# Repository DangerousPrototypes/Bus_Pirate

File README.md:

# Bus Pirate
The Bus Pirate is an open source hacker multi-tool that talks to electronic stuff. It's got a bunch of features an intrepid hacker might need to prototype their next project.

## Protocols
    
* 1-Wire
* I2C*
* SPI
* JTAG
* Asynchronous serial
* MIDI
* PC keyboard
* HD44780 LCD
* 2- and 3-wire libraries with bitwise pin control
* Scriptable binary bitbang, 1-Wire, I2C, SPI, and UART modes 

## Features

* 0-5.5volt tolerant pins
* 0-6volt measurement probe
* 1Hz-40MHz frequency measurement
* 1kHz - 4MHz pulse-width modulator, frequency generator
* On-board multi-voltage pull-up resistors
* On-board 3.3volt and 5volt power supplies with software reset
* Macros for common operations
* Bus traffic sniffers (SPI, I2C)
* A bootloader for easy firmware updates
* Transparent USB->serial mode
* 10Hz-1MHz low-speed logic analyzer
* Servo driver
* Can program many AVR microcontrollers
  * Supported by AVRdude
  * Can emulate the AVR STK500 v2 with alternate ST500 Clone firmware 
  * Programs FPGAs and CPLDs with alternate XSVF firmware
* Scriptable from Perl, Python, etc.
* Translations (currently Spanish and Italian)
* Public domain (Creative Commons Zero) source. Prototype with the Bus Pirate, then use the code in your project however you want. 

## Application Support
The Bus Pirate is used through a simple terminal interface, but these applications also support the Bus Pirate as a programming device, etc.

* [AVRDude] AVR programmer (AVRDude v5.8+, firmware v4 (any) or v5.9+)
* [OpenOCD] JTAG debugger
* [flashrom] bios/flash programmer 

# Purchasing

* Bus Pirate v4.0 - *Newer, more space for bigger firmwares*
  * Worldwide: <http://www.seeedstudio.com/depot/bus-pirate-v4-for-developers-p-740.html>
* Bus Pirate v3.6 - *Proven, more well tested*
  * Worldwide: <http://www.seeedstudio.com/depot/bus-pirate-v3-assembled-p-609.html?cPath=61_68>
  * USA: <https://www.adafruit.com/products/237?&main_page=product_info&cPath=8&products_id=237>
  * USA: <http://www.epictinker.com/Bus-Pirate-v3-assembled-p/thm180c4m.htm>
  * Germany: <http://www.watterott.com/en/Bus-Pirate>
  * Europe: <http://evola.fr/en/dangerous-prototypes/164-bus-pirate-v3-6.html>
  * USA: <https://anibit.com/product/ptt07001>
  * USA: <http://store.hackaday.com/products/buspirate-v3-6-thm180c4m>

[OpenOCD]: http://openocd.org
[AVRDude]: http://www.nongnu.org/avrdude
[flashrom]: https://www.flashrom.org/Flashrom

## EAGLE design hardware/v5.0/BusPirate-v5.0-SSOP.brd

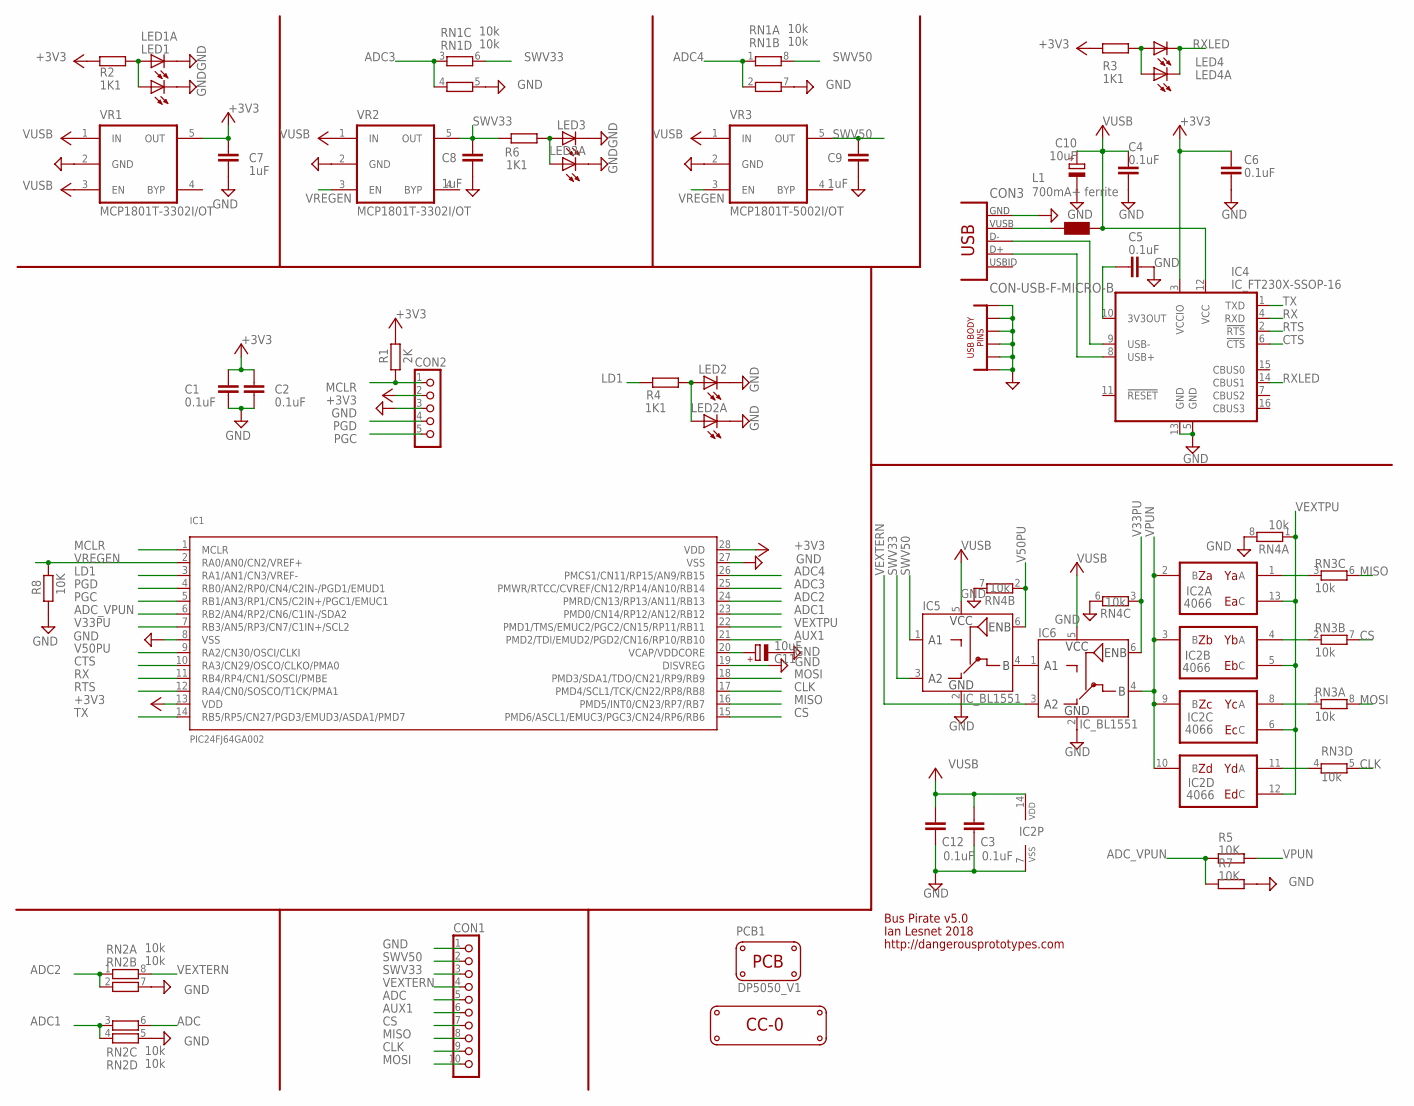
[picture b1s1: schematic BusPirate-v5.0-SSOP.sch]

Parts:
C1, C2, C3, C4, C5, C6, C12: 0.1uF; C603
C7, C8, C9: 1uF; C603
C10, C11: 10uF; SMC_A
CON1: CON_HEADER_1X10-RIGHT_ANGLED_PTH_SHROUDED; M1X10_MALE_RIGHT_ANGLES_PTH_SHROUDED
CON2: CON_HEADER_1X05-PTH; M1X5
CON3: CON-USB-F-MICRO-B; CON_USB_MICRO-B-1-MD05SMXXX-01
IC1: PIC24FJ64GA002; SSOP28
IC2: 4066; TSSOP14
IC4: IC_FT230X-SSOP-16; SSOP-16-FTDI
IC5, IC6: IC_BL1551; SC-70-6
L1: 700mA+ ferrite; WE-KI_0805_B
LED1, LED1A, LED2, LED2A, LED3, LED3A, LED4, LED4A: LED-0805; LED-805
LOGO1: LOGO_CC-0
PCB1: PCB_DP_SQUARE-5X5; DP5050_V1
R1: 2K; R603
R2, R3, R4, R6: 1K1; R603
R5, R7, R8: 10K; R603
RN1, RN2, RN3, RN4: 10k; RN8P-4R-CRA06S
VR1, VR2: MCP1801T-3302I/OT; SOT-23-5
VR3: MCP1801T-5002I/OT; SOT-23-5

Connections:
$N26: CON3.P1 (VUSB), L1.2 (1)
+3V3: C1.1, C2.1, C6.1, C7.1, CON2.2, IC1.13 (VDD), IC1.28 (VDD), IC4.3 (VCCIO), R1.2, R2.2, R3.2, VR1.5 (OUT)
ADC: CON1.5, RN2.6 (2)
ADC1: IC1.23 (PMD0/CN14/RP12/AN12/RB12), RN2.3 (1), RN2.4 (1)
ADC2: IC1.24 (PMRD/CN13/RP13/AN11/RB13), RN2.1, RN2.2 (1)
ADC3: IC1.25 (PMWR/RTCC/CVREF/CN12/RP14/AN10/RB14), RN1.3 (1), RN1.4 (1)
ADC4: IC1.26 (PMCS1/CN11/RP15/AN9/RB15), RN1.1, RN1.2 (1)
ADC_VPUN: IC1.6 (RB2/AN4/RP2/CN6/C1IN-/SDA2), R5.2, R7.2
AUX1: CON1.6, IC1.21 (PMD2/TDI/EMUD2/PGD2/CN16/RP10/RB10)
CLK: CON1.9, IC1.17 (PMD4/SCL1/TCK/CN22/RP8/RB8), RN3.5 (2)
CS: CON1.7, IC1.15 (PMD6/ASCL1/EMUC3/PGC3/CN24/RP6/RB6), RN3.7 (2)
CTS: IC1.10 (RA3/CN29/OSCO/CLKO/PMA0), IC4.6 (!CTS)
GND: C1.2, C2.2, C3.2, C4.2, C5.2, C6.2, C7.2, C8.2, C9.2, C10.-, C11.-, C12.2, CON1.1, CON2.3, CON3.GND1, CON3.GND2, CON3.GND3, CON3.GND4, CON3.GND5, CON3.GND6, CON3.P5 (GND), IC1.8 (VSS), IC1.19 (DISVREG), IC1.27 (VSS), IC2.7 (VSS), IC4.5 (GND), IC4.13 (GND), IC5.2 (GND), IC6.2 (GND), LED1.C, LED1A.C, LED2.C, LED2A.C, LED3.C, LED3A.C, R7.1, R8.1, RN1.5 (2), RN1.7 (2), RN2.5 (2), RN2.7 (2), RN4.6 (2), RN4.7 (2), RN4.8 (2), VR1.2 (GND), VR2.2 (GND), VR3.2 (GND)
LD1: IC1.3 (RA1/AN1/CN3/VREF-), R4.2
MCLR: CON2.1, IC1.1 (MCLR), R1.1
MISO: CON1.8, IC1.16 (PMD5/INT0/CN23/RP7/RB7), RN3.6 (2)
MOSI: CON1.10, IC1.18 (PMD3/SDA1/TDO/CN21/RP9/RB9), RN3.8 (2)
unnamed: IC2.11 (A), RN3.4 (1)
unnamed: IC2.8 (A), RN3.1
unnamed: C11.+, IC1.20 (VCAP/VDDCORE)
unnamed: IC2.4 (A), RN3.2 (1)
unnamed: IC2.1 (A), RN3.3 (1)
unnamed: LED2.A, LED2A.A, R4.1
unnamed: LED1.A, LED1A.A, R2.1
unnamed: C5.1, IC4.10 (3V3OUT)
unnamed: IC5.4 (B), IC6.1 (A1)
unnamed: LED4.A, LED4A.A, R3.1
unnamed: CON3.P3 (D+), IC4.8 (USB+)
unnamed: CON3.P2 (D-), IC4.9 (USB-)
unnamed: LED3.A, LED3A.A, R6.1
PGC: CON2.5, IC1.5 (RB1/AN3/RP1/CN5/C2IN+/PGC1/EMUC1)
PGD: CON2.4, IC1.4 (RB0/AN2/RP0/CN4/C2IN-/PGD1/EMUD1)
RTS: IC1.12 (RA4/CN0/SOSCO/T1CK/PMA1), IC4.2 (!RTS)
RX: IC1.11 (RB4/RP4/CN1/SOSCI/PMBE), IC4.4 (RXD)
RXLED: IC4.14 (CBUS1), LED4.C, LED4A.C
SWV33: C8.1, CON1.3, IC5.3 (A2), R6.2, RN1.6 (2), VR2.5 (OUT)
SWV50: C9.1, CON1.2, IC5.1 (A1), RN1.8 (2), VR3.5 (OUT)
TX: IC1.14 (RB5/RP5/CN27/PGD3/EMUD3/ASDA1/PMD7), IC4.1 (TXD)
V33PU: IC1.7 (RB3/AN5/RP3/CN7/C1IN+/SCL2), IC6.6 (ENB), RN4.3 (1)
V50PU: IC1.9 (RA2/CN30/OSCI/CLKI), IC5.6 (ENB), RN4.2 (1)
VEXTERN: CON1.4, IC6.3 (A2), RN2.8 (2)
VEXTPU: IC1.22 (PMD1/TMS/EMUC2/PGC2/CN15/RP11/RB11), IC2.5 (C), IC2.6 (C), IC2.12 (C), IC2.13 (C), RN4.1
VPUN: IC2.2 (B), IC2.3 (B), IC2.9 (B), IC2.10 (B), IC6.4 (B), R5.1
VREGEN: IC1.2 (RA0/AN0/CN2/VREF+), R8.2, VR2.3 (EN), VR3.3 (EN)
VUSB: C3.1, C4.1, C10.+, C12.1, IC2.14 (VDD), IC4.12 (VCC), IC5.5 (VCC), IC6.5 (VCC), L1.1 (2), VR1.1 (IN), VR1.3 (EN), VR2.1 (IN), VR3.1 (IN)

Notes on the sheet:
Bus Pirate v5.0
Ian Lesnet 2018
http://dangerousprototypes.com

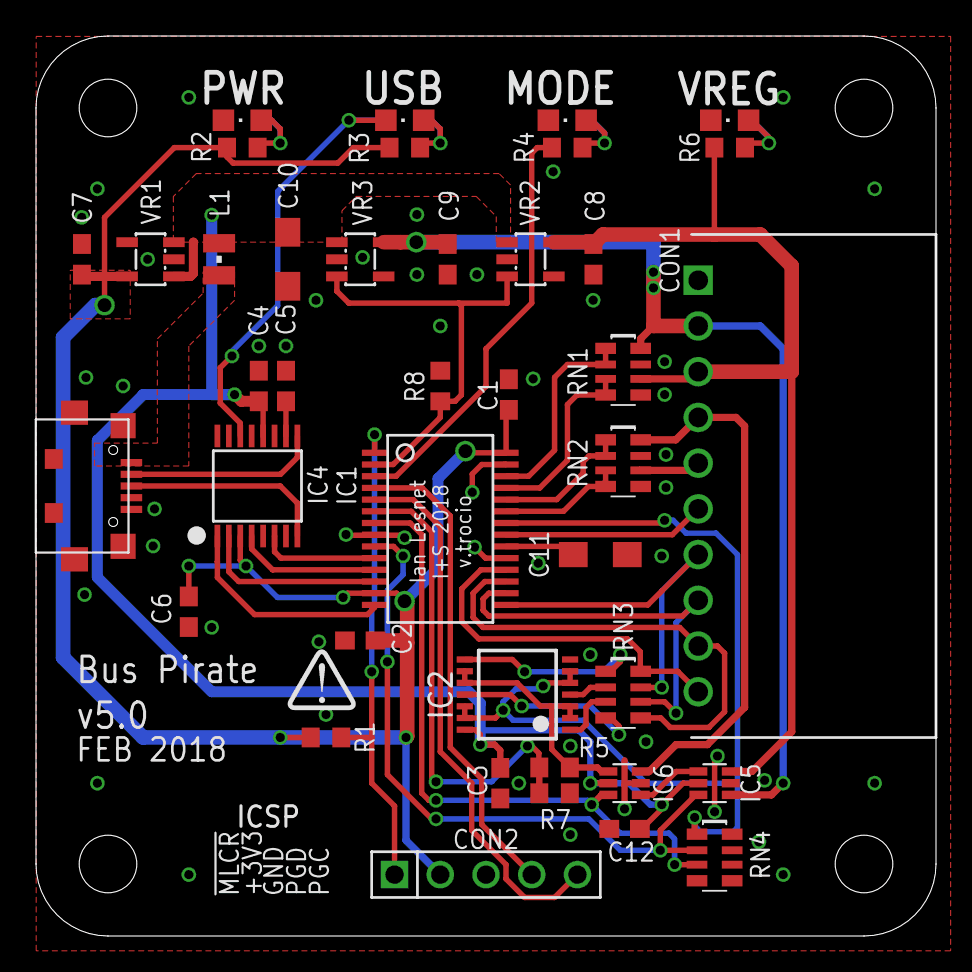
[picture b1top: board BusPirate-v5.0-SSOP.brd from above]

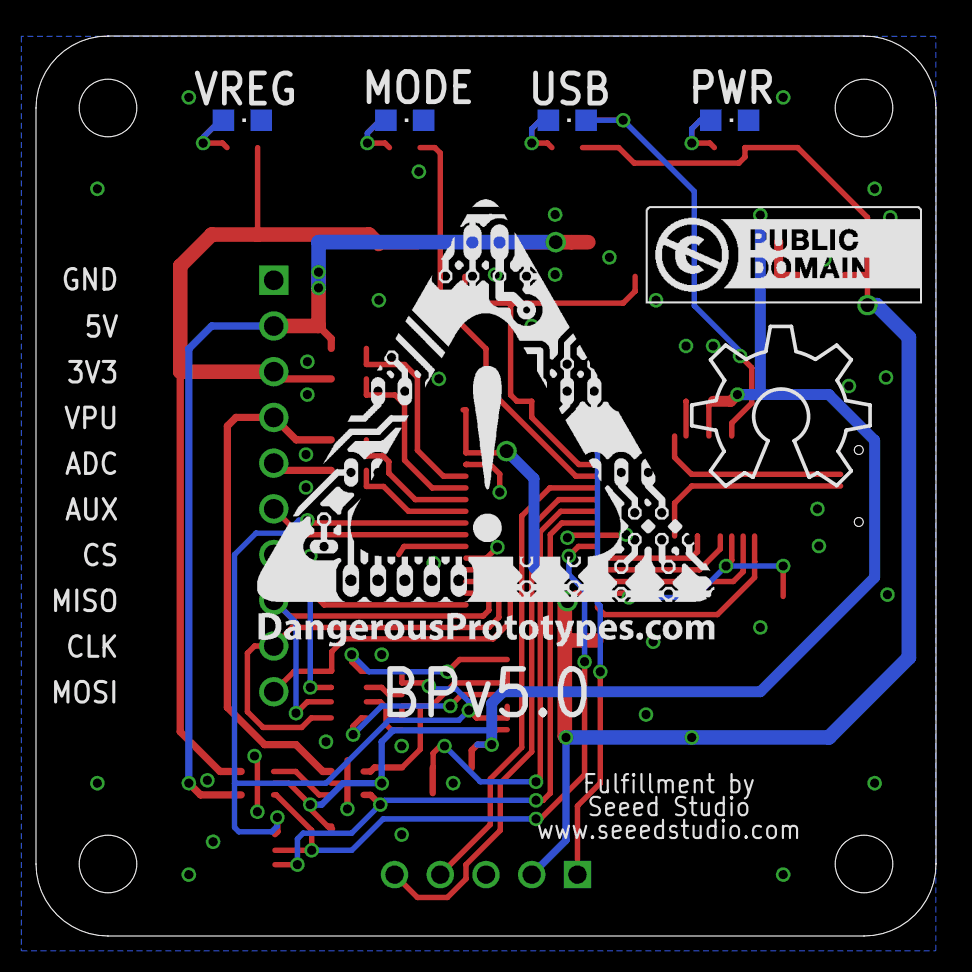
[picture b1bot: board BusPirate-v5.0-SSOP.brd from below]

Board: 2 copper layers, 50.0 x 50.0 mm, 49 parts (7 on the bottom side), 45 nets.

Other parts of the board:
U$1: DP-LOGO
U$2: OSHW_8X350_NOTEXT
U$3: DP_LOGO_ART_1X1

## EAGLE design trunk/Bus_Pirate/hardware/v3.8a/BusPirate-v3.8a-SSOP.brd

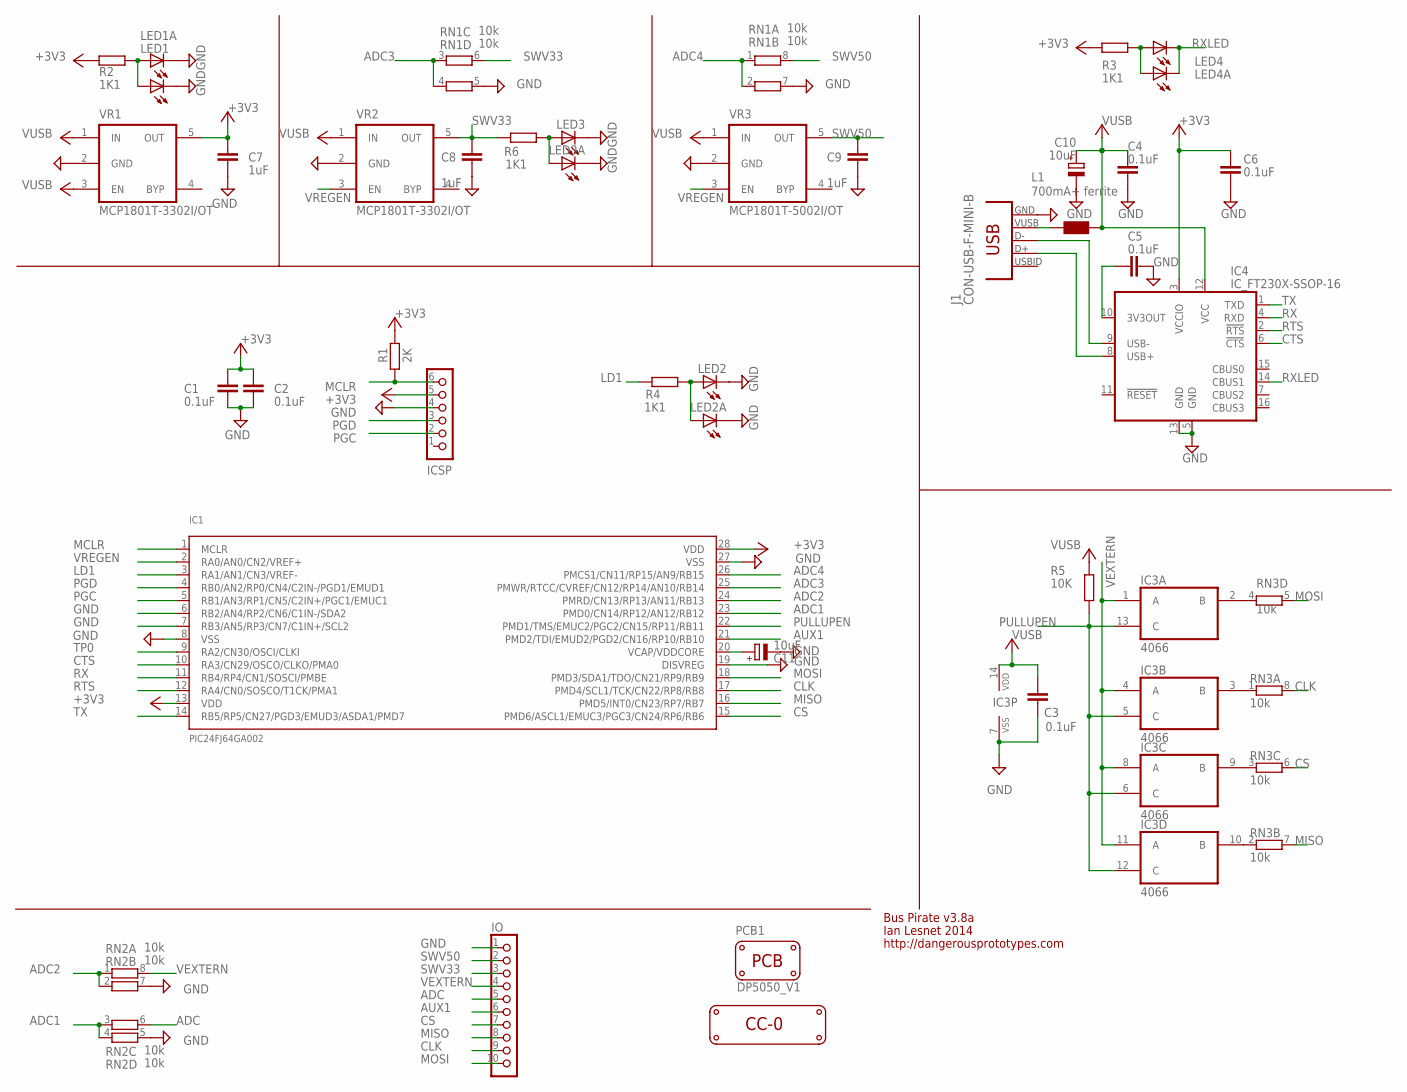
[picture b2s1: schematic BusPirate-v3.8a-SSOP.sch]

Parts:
C1, C2, C3, C4, C5, C6: 0.1uF; C603
C7, C8, C9: 1uF; C603
C10, C11: 10uF; SMC_A
IC1: PIC24FJ64GA002; SSOP28
IC3: 4066; TSSOP14
IC4: IC_FT230X-SSOP-16; SSOP-16-FTDI
ICSP: CON_HEADER_1X06-SMD-RIGHT-ANGLED; M1X6_MALE_RIGHT_ANGLED_SMD
IO: CON_HEADER_1X10-_RIGHTANGLED_SMD; M1X10_MALE_RIGHT_ANGLED_SMD
J1: CON-USB-F-MINI-B; CONN_USB_MINI-B
L1: 700mA+ ferrite; WE-KI_0805_B
LED1, LED1A, LED2, LED2A, LED3, LED3A, LED4, LED4A: LED-0603; LED-603
LOGO1: LOGO_CC-0
PCB1: PCB_DP_SQUARE-5X5; DP5050_V1
R1: 2K; R603
R2, R3, R4, R6: 1K1; R603
R5: 10K; R603
RN1, RN2, RN3: 10k; RN8P-4R-CRA06S
VR1, VR2: MCP1801T-3302I/OT; SOT-23-5
VR3: MCP1801T-5002I/OT; SOT-23-5

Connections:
$N26: J1.VUSB, L1.2 (1)
+3V3: C1.1, C2.1, C6.1, C7.1, IC1.13 (VDD), IC1.28 (VDD), IC4.3 (VCCIO), ICSP.5, R1.2, R2.2, R3.2, VR1.5 (OUT)
ADC: IO.5, RN2.6 (2)
ADC1: IC1.23 (PMD0/CN14/RP12/AN12/RB12), RN2.3 (1), RN2.4 (1)
ADC2: IC1.24 (PMRD/CN13/RP13/AN11/RB13), RN2.1, RN2.2 (1)
ADC3: IC1.25 (PMWR/RTCC/CVREF/CN12/RP14/AN10/RB14), RN1.3 (1), RN1.4 (1)
ADC4: IC1.26 (PMCS1/CN11/RP15/AN9/RB15), RN1.1, RN1.2 (1)
AUX1: IC1.21 (PMD2/TDI/EMUD2/PGD2/CN16/RP10/RB10), IO.6
CLK: IC1.17 (PMD4/SCL1/TCK/CN22/RP8/RB8), IO.9, RN3.8 (2)
CS: IC1.15 (PMD6/ASCL1/EMUC3/PGC3/CN24/RP6/RB6), IO.7, RN3.6 (2)
CTS: IC1.10 (RA3/CN29/OSCO/CLKO/PMA0), IC4.6 (!CTS)
GND: C1.2, C2.2, C3.2, C4.2, C5.2, C6.2, C7.2, C8.2, C9.2, C10.-, C11.-, IC1.6 (RB2/AN4/RP2/CN6/C1IN-/SDA2), IC1.7 (RB3/AN5/RP3/CN7/C1IN+/SCL2), IC1.8 (VSS), IC1.19 (DISVREG), IC1.27 (VSS), IC3.7 (VSS), IC4.5 (GND), IC4.13 (GND), ICSP.4, IO.1, J1.GND, LED1.C, LED1A.C, LED2.C, LED2A.C, LED3.C, LED3A.C, RN1.5 (2), RN1.7 (2), RN2.5 (2), RN2.7 (2), VR1.2 (GND), VR2.2 (GND), VR3.2 (GND)
LD1: IC1.3 (RA1/AN1/CN3/VREF-), R4.2
MCLR: IC1.1 (MCLR), ICSP.6, R1.1
MISO: IC1.16 (PMD5/INT0/CN23/RP7/RB7), IO.8, RN3.7 (2)
MOSI: IC1.18 (PMD3/SDA1/TDO/CN21/RP9/RB9), IO.10, RN3.5 (2)
unnamed: IC3.2 (B), RN3.4 (1)
unnamed: IC3.9 (B), RN3.3 (1)
unnamed: C11.+, IC1.20 (VCAP/VDDCORE)
unnamed: IC3.10 (B), RN3.2 (1)
unnamed: IC3.3 (B), RN3.1
unnamed: LED2.A, LED2A.A, R4.1
unnamed: LED1.A, LED1A.A, R2.1
unnamed: C5.1, IC4.10 (3V3OUT)
unnamed: LED4.A, LED4A.A, R3.1
unnamed: IC4.8 (USB+), J1.D+
unnamed: IC4.9 (USB-), J1.D-
unnamed: LED3.A, LED3A.A, R6.1
PGC: IC1.5 (RB1/AN3/RP1/CN5/C2IN+/PGC1/EMUC1), ICSP.2
PGD: IC1.4 (RB0/AN2/RP0/CN4/C2IN-/PGD1/EMUD1), ICSP.3
PULLUPEN: IC1.22 (PMD1/TMS/EMUC2/PGC2/CN15/RP11/RB11), IC3.5 (C), IC3.6 (C), IC3.12 (C), IC3.13 (C), R5.2
RTS: IC1.12 (RA4/CN0/SOSCO/T1CK/PMA1), IC4.2 (!RTS)
RX: IC1.11 (RB4/RP4/CN1/SOSCI/PMBE), IC4.4 (RXD)
RXLED: IC4.14 (CBUS1), LED4.C, LED4A.C
SWV33: C8.1, IO.3, R6.2, RN1.6 (2), VR2.5 (OUT)
SWV50: C9.1, IO.2, RN1.8 (2), VR3.5 (OUT)
TP0: IC1.9 (RA2/CN30/OSCI/CLKI)
TX: IC1.14 (RB5/RP5/CN27/PGD3/EMUD3/ASDA1/PMD7), IC4.1 (TXD)
VEXTERN: IC3.1 (A), IC3.4 (A), IC3.8 (A), IC3.11 (A), IO.4, RN2.8 (2)
VREGEN: IC1.2 (RA0/AN0/CN2/VREF+), VR2.3 (EN), VR3.3 (EN)
VUSB: C3.1, C4.1, C10.+, IC3.14 (VDD), IC4.12 (VCC), L1.1 (2), R5.1, VR1.1 (IN), VR1.3 (EN), VR2.1 (IN), VR3.1 (IN)

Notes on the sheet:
Bus Pirate v3.8a
Ian Lesnet 2014
http://dangerousprototypes.com

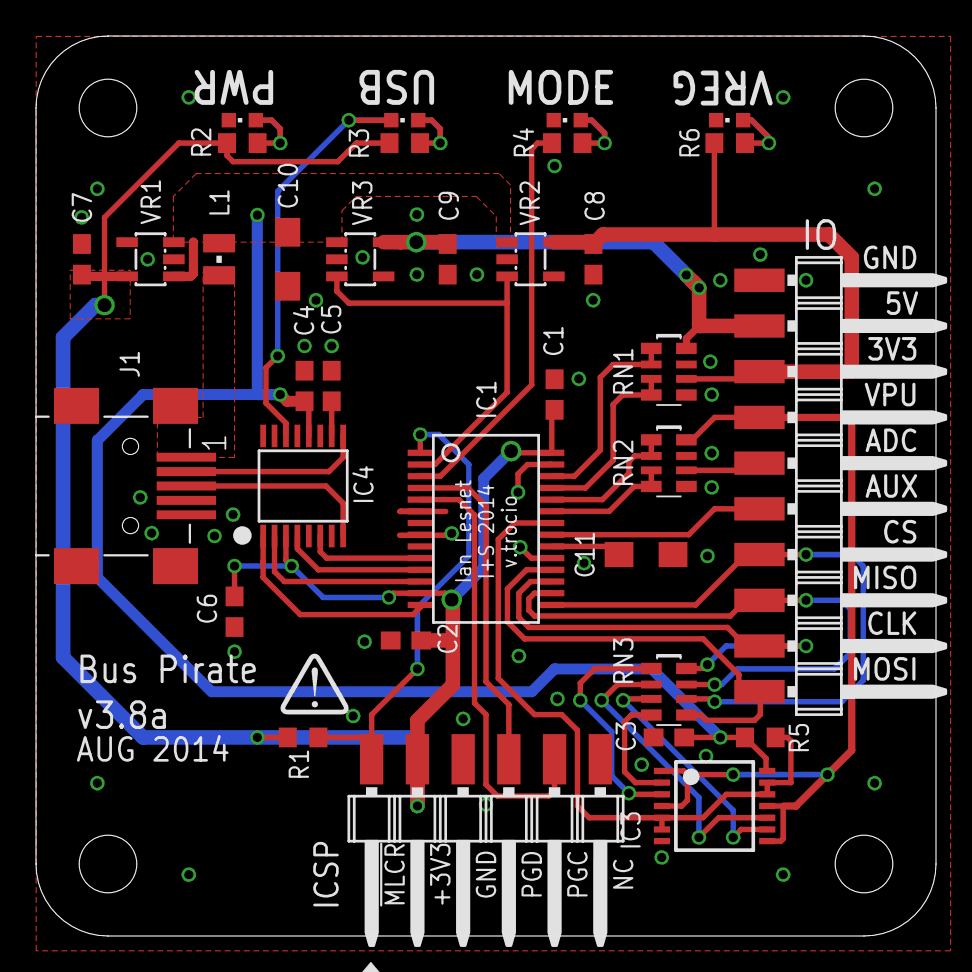
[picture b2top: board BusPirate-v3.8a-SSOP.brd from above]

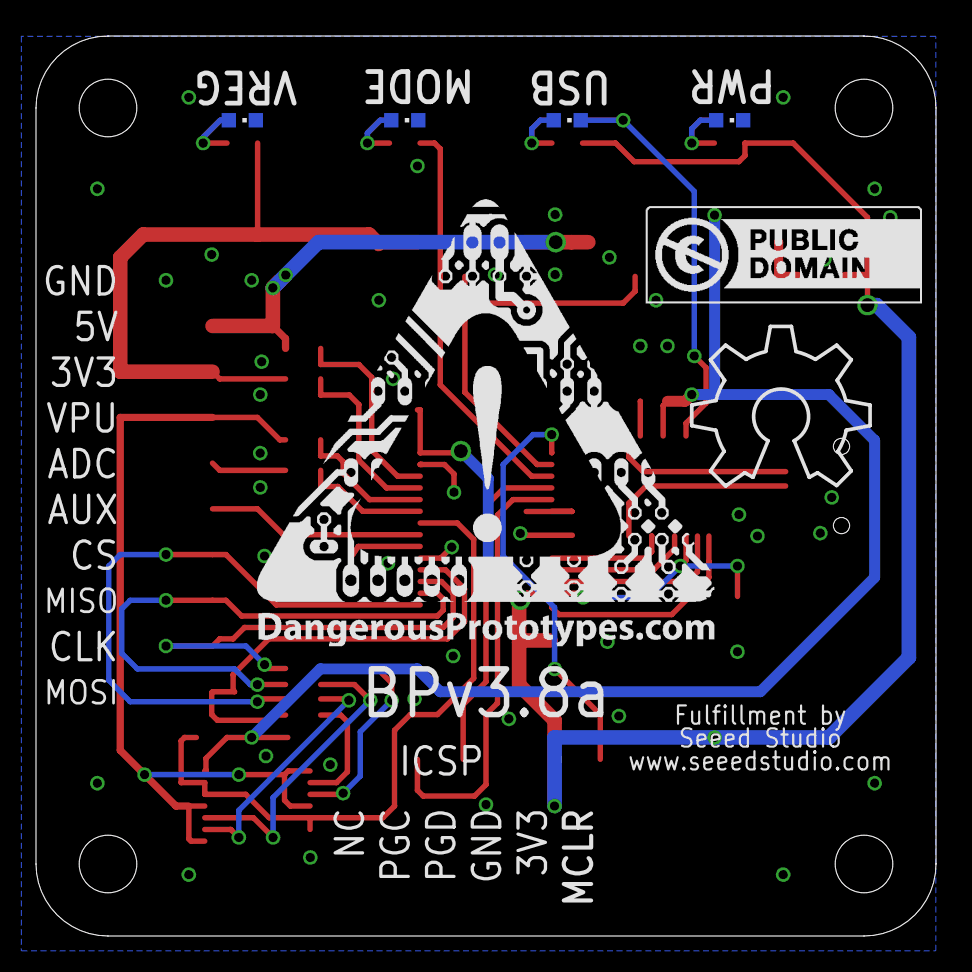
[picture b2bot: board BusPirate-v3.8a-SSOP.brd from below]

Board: 2 copper layers, 50.0 x 50.0 mm, 43 parts (7 on the bottom side), 40 nets.

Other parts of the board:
U$1: DP-LOGO
U$2: OSHW_8X350_NOTEXT
U$3: DP_LOGO_ART_1X1

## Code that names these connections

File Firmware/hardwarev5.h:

/*
 * This file is part of the Bus Pirate project (http://code.google.com/p/the-bus-pirate/).
 *
 * Written and maintained by the Bus Pirate project.
 *
 * To the extent possible under law, the project has
 * waived all copyright and related or neighboring rights to Bus Pirate. This
 * work is published from United States.
 *
 * For details see: http://creativecommons.org/publicdomain/zero/1.0/.
 *
 *    This program is distributed in the hope that it will be useful,
 *    but WITHOUT ANY WARRANTY; without even the implied warranty of
 *    MERCHANTABILITY or FITNESS FOR A PARTICULAR PURPOSE.
 */
//this profile is for the Bus Pirate v5 hardware from dangerousprototypes.com
#define BP_VERSION_STRING "Bus Pirate v5."// (Seeed Studio)"
#define BP_VERSION "v5"

#define NUM_OF_SUMP_CHANNELS 5

//set the pin to use for POST detection
#define BP_POST 	PORTBbits.RB0
#define BP_POST_DIR TRISBbits.TRISB0

//this configures the placement of the serial port for 
//the PC side terminal interface
//the other modules should be similarly abstracted, but since v0A and v1a share pins, it doesn't mater
#define BP_TERM_TX		U1TX_IO;
#define BP_TERM_TX_RP  	RPOR2bits.RP4R
#define BP_TERM_RX		RPINR18bits.U1RXR
#define BP_TERM_RX_RP	5

//this is a different type of pin identifier used by the bitbang library
#define AUX		0b10000000000 //RB10 on v1, 2, 2go, 3 (not v0)
#define MOSI 	0b1000000000  //RB9
#define CLK 	0b100000000    //RB8
#define MISO 	0b10000000 //RB7
#define CS 		0b1000000 //RB6
#define IOPOR 	PORTB
#define IOLAT	LATB
#define IODIR	TRISB
#define ALLIO  (MOSI+CLK+MISO+CS)

//these macros set the pin IO used in each module
#define BP_MOSI 		PORTBbits.RB9
#define BP_CLK 			PORTBbits.RB8
#define BP_MISO 		PORTBbits.RB7
#define BP_CS 			PORTBbits.RB6
#define BP_AUX0 			PORTBbits.RB10 //moved pin5 (AUX) to RB10
#define BP_LEDMODE		PORTAbits.RA1 //single MODE led on v2a
#define BP_VREGEN		PORTAbits.RA0 //single vreg enable pin on v2a
#define BP_PUVSELEXT	PORTBbits.RB11 //Pull-up pin on V2a
#define BP_PGD			PORTBbits.RB0 //PGD pin on programming header
//v5 addition
#define BP_PUVSEL33             PORTBbits.RB3
#define BP_PUVSEL50             PORTAbits.RA2

//these macros set the direction registers for each IO pin
#define BP_MOSI_DIR 	TRISBbits.TRISB9
#define BP_CLK_DIR 		TRISBbits.TRISB8
#define BP_MISO_DIR 	TRISBbits.TRISB7
#define BP_CS_DIR 		TRISBbits.TRISB6
#define BP_AUX0_DIR 	TRISBbits.TRISB10
#define BP_LEDMODE_DIR	TRISAbits.TRISA1
#define BP_VREGEN_DIR	TRISAbits.TRISA0
#define BP_PUVSELEXT_DIR TRISBbits.TRISB11
#define BP_PGD_DIR		TRISBbits.TRISB0
//v5 addition
#define BP_PUVSEL33_DIR         TRISBbits.TRISB3
#define BP_PUVSEL50_DIR         TRISAbits.TRISA2


//Open drain/high impedance pin setup
#define BP_MOSI_ODC 	ODCBbits.ODB9
#define BP_CLK_ODC 		ODCBbits.ODB8
#define BP_MISO_ODC 	ODCBbits.ODB7
#define BP_CS_ODC 		ODCBbits.ODB6
#define BP_AUX0_ODC 		ODCBbits.ODB10

//Change notice assignment
#define BP_MOSI_CN		CNEN2bits.CN21IE
#define BP_CLK_CN		CNEN2bits.CN22IE

//ADC assignment
#define BP_ADC_PROBE 12
#define BP_ADC_3V3 10
#define BP_ADC_5V0 9
#define BP_ADC_VPU 11
#define BP_ADC_VPUN 4 //ADC connected to 74hct4066 pullup voltage output

//calculate the acceptable range of voltages for the power supplies
//these values will be compared to the ADC reading from the supply monitor
#define V5BASE 0x307 //(((5/2)/3.3)*1024))
#define V5H	V5BASE+0x50
#define V5L V5BASE-0x50

#define V33BASE 0x200 //(((3.3/2)/3.3)*1024))
#define V33H	V33BASE+0x50
#define V33L	V33BASE-0x50

#define ADCON() AD1CON1bits.ADON = 1 // turn ADC ON 
#define ADCOFF() AD1CON1bits.ADON = 0 // turn ADC OFF 

//ADC pin configuration
#define BP_ADC_PROBE_CFG AD1PCFGbits.PCFG12 //B12/AN12/ADC1/EXT 
#define BP_ADC_3V3_CFG AD1PCFGbits.PCFG10 //B14/AN10/ADC3/33V 
#define BP_ADC_5V0_CFG AD1PCFGbits.PCFG9 //B15/AN9/ADC4/50V
#define BP_ADC_VPU_CFG AD1PCFGbits.PCFG11 //B13/AN11/ADC2/Vextpullup
#define BP_ADC_VPUN_CFG AD1PCFGbits.PCFG4 //B2/AN4/ADC5/VPU net

#define BP_ADC_PINSETUP() BP_ADC_PROBE_CFG=0;BP_ADC_3V3_CFG=0;BP_ADC_5V0_CFG=0;BP_ADC_VPU_CFG=0;BP_ADC_VPUN_CFG=0

//flow control connections for FTDI chip
//used in uart brige
#define FTDI_RTS_DIR TRISAbits.TRISA4
#define FTDI_RTS PORTAbits.RA4
#define FTDI_CTS_DIR TRISAbits.TRISA3
#define FTDI_CTS PORTAbits.RA3

//defines the PPS input/output for MISO and MOSI pins
#define BP_MISO_RPIN 7
#define BP_MISO_RPOUT RPOR3bits.RP7R
#define BP_MOSI_RPIN 9
#define BP_MOSI_RPOUT RPOR4bits.RP9R

//define the PPS input/output for the AUX pin
#define BP_AUX_RPIN 10	
#define BP_AUX_RPOUT RPOR5bits.RP10R
#define BP_CS_RPIN 6
#define BP_CS_RPOUT RPOR5bits.RP6R

//define the PPS input/output for CLK pin
#define BP_CLK_RPIN 8
#define BP_CLK_RPOUT RPOR4bits.RP8R

//pseudofunctions for pullup resistors
//v5 has selectable pullups (3.3v, 5v, external)
//it uses the 74HCT4066 with has a 2.0v on level, so instead of pulling high with VUSB, 
//we drive it directly with the bus pirate pin. 
//pullup voltage enable/disable
//BL1551 selects source of pullup. 
//BP_PUVSELEXT turns pullups off and on
//V33PU    	|	V50PU	|	Source
// 0		|	X		|	Vexternal
// 1		|	0		|	SWV33
// 1		|	1		|	SWV50
#define BP_PULLUP_SETUP() BP_PUVSELEXT=0;BP_PUVSELEXT_DIR=0; BP_PUVSEL33=0; BP_PUVSEL33_DIR=0; BP_PUVSEL50=0; BP_PUVSEL50_DIR=0
#define BP_PULLUP_OFF() BP_PUVSELEXT=0; BP_PUVSEL33=0; BP_PUVSEL50=0
#define BP_EXTPU_ON()          BP_PUVSEL33=0; BP_PUVSEL50=0; BP_PUVSELEXT=1
#define BP_3V3PU_ON()          BP_PUVSEL33=1; BP_PUVSEL50=0; BP_PUVSELEXT=1
#define BP_5VPU_ON()           BP_PUVSEL33=1; BP_PUVSEL50=1; BP_PUVSELEXT=1

//pseudofunctions for voltage regulator switch
#define BP_VREG_ON() BP_VREGEN_DIR=0; BP_VREGEN=1
#define BP_VREG_OFF() BP_VREGEN_DIR=0; BP_VREGEN=0

#define BP_MODELED_ON() LATA|=0b10
#define BP_MODELED_OFF()LATA&=(~0b10)

//define device ID and revision memory location
#define DEV_ADDR_UPPER	0x00FF
#define DEV_ADDR_TYPE	0x0000
#define DEV_ADDR_REV	0x0002
#define CFG_ADDR_UPPER 0x0000
#define BL_ADDR_VER		0xABFA //location of the bootloader version info
#define CFG_ADDR_1     0xABFC
#define CFG_ADDR_2     0xABFE

// Peripheral Pin Select Outputs
#define NULL_IO		0
#define C1OUT_IO	1
#define C2OUT_IO	2
#define U1TX_IO		3
#define U1RTS_IO	4
#define U2TX_IO		5
#define U2RTS_IO	6
#define SDO1_IO		7
#define SCK1OUT_IO	8
#define SS1OUT_IO	9
#define SDO2_IO		10
#define SCK2OUT_IO	11
#define SS2OUT_IO	12
#define OC1_IO		18
#define OC2_IO		19
#define OC3_IO		20
#define OC4_IO		21
#define OC5_IO		22

#define PIC_REV_A3	0x3003
#define PIC_REV_B4	0x3042
#define PIC_REV_B5	0x3043
#define PIC_REV_B8	0x3046

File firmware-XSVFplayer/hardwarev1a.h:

/*
 * This file is part of the Bus Pirate project (buspirate.com).
 *
 * Originally written by hackaday.com <legal@hackaday.com>
 *
 * To the extent possible under law, hackaday.com <legal@hackaday.com> has
 * waived all copyright and related or neighboring rights to Bus Pirate. This
 * work is published from United States.
 *
 * For details see: http://creativecommons.org/publicdomain/zero/1.0/.
 *
 *    This program is distributed in the hope that it will be useful,
 *    but WITHOUT ANY WARRANTY; without even the implied warranty of
 *    MERCHANTABILITY or FITNESS FOR A PARTICULAR PURPOSE.
 *
 */

//this hardware profile is for the second, surface mount Bus Pirate.
//http://hackaday.com/2009/01/22/how-to-bus-pirate-v1-improved-universal-serial-interface

#define BP_VERSION_STRING "Hack a Day Bus Pirate v1a"
#define BP_VERSION "v1a"

//this configures the placement of the serial port for 
//the PC side terminal interface
//the other modules should be similarly abstracted, but since v0A and v1a share pins, it doesn't mater
//when we move to a USB PIC, we'll need to do that....
#define BP_TERM_TX		U1TX_IO;
#define BP_TERM_TX_RP  	RPOR1bits.RP2R
#define BP_TERM_RX		RPINR18bits.U1RXR
#define BP_TERM_RX_RP	3

//these macros set the pin IO used in each module
#define BP_MOSI 		PORTBbits.RB9
#define BP_CLK 			PORTBbits.RB8
#define BP_MISO 		PORTBbits.RB7
#define BP_CS 			PORTBbits.RB6
#define BP_AUX 			PORTBbits.RB10 //moved pin5 (AUX) to RB10
#define BP_PIN6			PORTBbits.RB11
#define BP_LEDMODE		PORTBbits.RB4
#define BP_LEDPWR		PORTAbits.RA3
#define BP_EN50V		PORTAbits.RA4
#define BP_EN33V		PORTBbits.RB5

//these macros set the direction registers for each IO pin
#define BP_MOSI_DIR 	TRISBbits.TRISB9
#define BP_CLK_DIR 		TRISBbits.TRISB8
#define BP_MISO_DIR 	TRISBbits.TRISB7
#define BP_CS_DIR 		TRISBbits.TRISB6
#define BP_AUX_DIR 		TRISBbits.TRISB10
#define BP_PIN6_DIR 	TRISBbits.TRISB11
#define BP_LEDMODE_DIR		TRISBbits.TRISB4
#define BP_LEDPWR_DIR		TRISAbits.TRISA3
#define BP_EN50V_DIR	TRISAbits.TRISA4
#define BP_EN33V_DIR	TRISBbits.TRISB5

//Open drain/high impedance pin setup
#define BP_MOSI_ODC 	ODCBbits.ODB9
#define BP_CLK_ODC 		ODCBbits.ODB8
#define BP_MISO_ODC 	ODCBbits.ODB7
#define BP_CS_ODC 		ODCBbits.ODB6
#define BP_AUX_ODC 		ODCBbits.ODB10

//define the PPS input/output for the AUX pin
#define BP_AUX_RPIN 10	
#define BP_AUX_RPOUT RPOR5bits.RP10R
#define BP_CS_RPIN 6
#define BP_CS_RPOUT RPOR5bits.RP6R

//pseudo function to reset pins to hizstate
//pseudofunctions for voltage regulator switch
#define BP_VREG_ON() BP_EN50V_DIR=0; BP_EN50V=1; BP_EN33V_DIR=0; BP_EN33V=1
#define BP_VREG_OFF() BP_EN50V_DIR=0; BP_EN50V=0; BP_EN33V_DIR=0; BP_EN33V=0

// Peripheral Pin Select Outputs
#define NULL_IO		0
#define C1OUT_IO	1
#define C2OUT_IO	2
#define U1TX_IO		3
#define U1RTS_IO	4
#define U2TX_IO		5
#define U2RTS_IO	6
#define SDO1_IO		7
#define SCK1OUT_IO	8
#define SS1OUT_IO	9
#define SDO2_IO		10
#define SCK2OUT_IO	11
#define SS2OUT_IO	12
#define OC1_IO		18
#define OC2_IO		19
#define OC3_IO		20
#define OC4_IO		21
#define OC5_IO		22

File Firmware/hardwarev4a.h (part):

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#define AUX0                    0b100000 //B5
#define SUMP_SPARE6             0b1000000 //B6
#define SUMP_SPARE7             0b10000000 //B7
#define AUX1                    0b100000000 //B8

#define IOPOR                   PORTD
#define IOLAT                   LATD
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#define BP_CLK                  PORTDbits.RD2
#define BP_MISO                 PORTDbits.RD3
#define BP_CS                   PORTDbits.RD4
#define BP_AUX0                 PORTDbits.RD5 //moved pin5 (AUX) to RB10
#define BP_LEDMODE              PORTBbits.RB8 //single MODE led on v2a
#define BP_VREGEN               PORTBbits.RB9 //single vreg enable pin on v2a
#define BP_PULLUP               PORTEbits.RE4 //Pull-up pin on V2a
#define BP_PGD                  PORTBbits.RB7 //PGD pin on programming header

//new in v4
#define BP_LEDUSB               PORTBbits.RB10
#define BP_BUTTON               PORTCbits.RC14
#define BP_AUX1                 PORTDbits.RD8 
#define BP_AUX2                 PORTDbits.RD0 
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//#define BP_CLK                PORTDbits.RD2
//#define BP_MISO               PORTDbits.RD3
//#define BP_CS                 PORTDbits.RD4
#define BP_AUX_LAT              LATDbits.LATD5 //moved pin5 (AUX) to RB10
//#define BP_LEDMODE            PORTBbits.RB8 //single MODE led on v2a
//#define BP_VREGEN             PORTBbits.RB9 //single vreg enable pin on v2a
//#define BP_PULLUP             PORTEbits.RE4 //Pull-up pin on V2a
//#define BP_PGD                PORTBbits.RB7 //PGD pin on programming header

//new in v4
//#define BP_LEDUSB             PORTBbits.RB10
//#define BP_BUTTON             PORTCbits.RC14
//#define BP_AUX1               PORTFbits.RF5 
//#define BP_AUX2               PORTFbits.RF4 
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#define BP_ADC_3V3_CFG          AD1PCFGbits.PCFG1 //AN0/ADC3/33V
#define BP_ADC_5V0_CFG          AD1PCFGbits.PCFG0 //AN2/ADC4/50V
#define BP_ADC_VPU_CFG          AD1PCFGbits.PCFG5 //AN5/ADC2/Vextpullup
#define BP_ADC_USB_CFG          AD1PCFGbits.PCFG15 //AN15/ADC5/Vusb

#define BP_ADC_PINSETUP()       BP_ADC_PROBE_CFG=0;BP_ADC_3V3_CFG=0;BP_ADC_5V0_CFG=0;BP_ADC_VPU_CFG=0;BP_ADC_USB_CFG=0

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
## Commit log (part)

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2012-09-12 Updated ATX PSU v1.3 Added ATX PSU v2 board. Board was made in KiCAD
2012-09-12 first commit of DP KiCAD part library
2012-09-13 .lib and .mod files converted using eagle2kicad-0.d.ulp from http://www.modulbot.com/download.html Fixed undefined DRAW command when loading to symbol library to KiCAD
2012-09-17 add bus pirate v5c board, enlarge ADC Input label
2012-09-20 Bus Pirate v4 Sick of Beige case laser cutting files and partlist(BOM)
2012-09-21 SoB case generator plugin from Tayken
2012-09-24 Done the changes related to global->instance variables suggested by Jim, corrected some variable name typos and got rid of console debug messages.
2012-09-24 Added new Logic shrimp v2b, this version uses 23LC1024 SRAM
2012-09-25 initial Smoke Tester project folder
2012-09-25 add schematic image
2012-09-26 swapped drain and source pin of the p-mosfet controlling fuse blown switch
2012-10-01 Smoke Tester 3D model and renders
2012-10-02 Added MIC2027, D8035E VFD and update Arduino outline header placement outline
2012-10-07 adding an assortment of 3d models. They should all have origins centered properly about the pins. These were not checked thoroughly, but do appear to be generally correct. Most models are tweaked fro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
    The QFN32 is original and should be extremely easy to scale and accommodate other numbers of pins.
2012-10-08 Added: TD62783 8 Ch high side voltage source driver Updated: 74595 shift register symbol, changed pin names of SCLK, SDA, LATCH and RST
2012-10-08 Added: PTH variant of 2.1mm DC Barrel Connector with milled hole pads
2012-10-09 added series diode on Vusb in and Vin header, moved C8 beside SD holder
2012-10-10 first cut at molex KK series connectors. The 1x2 should be modeled in such a way that it's side stackable, so it will be easy to make additional even numbered connectors. These were based on a model 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
    These should be "close enough" for most purposes, alignment appears to be off a bit on the 4pos header though.
2012-10-10 Bourns TC33X-2-104E 3mm surface mount trim pot
2012-10-10 Added: 3D models for 2 trough-hole IC and a metalized Capacitor.
2012-10-11 added version 2
2012-10-16 rearanged SID SVN, and aded the mauf resources and sales page foleder...as wlell as the sales page txt
2012-10-18 correcting the naming for the 2512 resistor model
2012-10-18 Added device: MicrosSD fold type socket, PIC24F16KA102, 1x2 SMD solder jumper. fix Arduino 1x8 header containing pin 8 - 13, offset ed location.
2012-10-18 Bus Blaster v4 test buffer project
2012-10-19 fix PIC24F16KA102 vector text overlap on its symbol Add SOIC-14 package on PIC16F1823
2012-10-22 Soldering Iron Driver renderings and 3D model
2012-10-25 add: FT230x_LTC4053_BB
2012-10-25 add project: FT230x_LTC4053_BB_proto_area.v1a
2012-10-28 Retrieved demo board v5 files from previous revision, and renamed the wrongly named v5a into proper names
2012-10-30 added DIL-28 PTH to SMD socket
2012-10-31 Added manufacturing files for updated ATX board acrylic case
2012-11-05 added: 4.5 x 4.5 SMD Trimmer, model 3314G
2012-11-07 added right angled 0.1inch 1x06 male header. expanded M1X4, M1X6, M1X8 pads to 1.632mm and drill size to 1.02mm
2012-11-13 added a 1x06 right angled header and a 2x03 SMD straight male headers.
2012-11-15 initial xQFP protoboards folder
2012-11-19 BP v4d, buspirate v4 fitted into a bigger DP PCB (DP7043)
2012-11-22 added v2.1, LCD_Backpack_1.8_TFT with pogo footprint ICSP
2012-11-22 fix, ICSP pogo pin programmer footprint by adding a pad on the keyhole for a key pogo pin to be soldered
2012-12-05 commit PIC TQFP-100 breakout v1 and v2
2012-12-06 added protoboard with 0.50mm xQFP
2012-12-07 added BP v4e, fix odd angled placement, no 45 degrees placement anymore. replaced ICSP header with miniature ICSP footprint
2012-12-07 updated 0.5, 0.65 and 0.8 xQFP protoboards by adding a USB footprint. 2-3 SOT-23-6 footprints were removed to fit the usb
2012-12-10 added a 6 way SOLO stacker connector and footprint
2012-12-12 added dual xQFP pitch protoboards, pitch combined are 0.50 + 0.65 mm, 0.80 + 0.50 mm and 0.80 + 0.65 mm. these boards were also having a micro usb footprint under its mini-b footprint
2012-12-12 added TSSOP-20 variant of TXB0108, voltage level translator
2012-12-20 added: 1x1 PTH hole for protoboard filler changed "board name" of DP standard PCB name(on the bottom) to ">NAME" so it will now be smashable a can be moved around.
2012-12-20 revert back DP Standard PCB with the label name indicating its PCB size
2013-01-07 added 0603 SMD LED, 1x02 and 1x03 right angled 0.1 inch pitched PTH header
2013-01-08 renamed xQFP_protoboard_080_050.v1 to v2
2013-01-10 Bus Pirate - AUXpin.c. Cleaned the code a bit, deleted a huge commented out section, and applyed the patch in issue #65 http://dangerousprototypes.com/track/view.php?id=65
2013-01-11 Bus Pirate firmware -v4 pull up voltage control add to bin protocol. as per issue 63 http://dangerousprototypes.com/track/view.php?id=63 patch available at the link above, and is applied to rev2082
2013-01-14 A slight change in variable definition in procMenu.c, and indent fix in I2C.c
2013-01-17 Bus Pirate firmware version change to v6.3 + Issues 57 and 24 ...
    Version change to 6.3 - We're clearing out the backlog of issues so it's a perfect time for a version change to 6.3
    issue 57
    http://dangerousprototypes.com/track/view.php?id=57
    a clutch is added between the setup process and the start of using a protocol, Once setup is done all the pins are still at HiZ. only when you type in the 'W' commend does the clutch engage - pins ar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
    issue 24
    http://dangerousprototypes.com/track/view.php?id=24
2013-01-18 HEx files ready for upload through bootloader for BP v3 and v4 6.3r2088
2013-01-25 Added PTH 2x7 0.1" header, fix TSSOP-20 footprint pad arrangement, fix 74AC573 TSSOP-20 pin numbering
2013-01-25 Test commit.
2013-01-25 * Initial check-in.
2013-01-25 * Added bootloader.
2013-01-25 * Added Gerber files.
2013-01-27 * Added color scheme for logic shrimp probe cables.
2013-01-28 Bus Pirate Firmware - issue 53. Basic scripting engine put back into v6.2.... http://dangerousprototypes.com/track/view.php?id=53
2013-01-31 * Implemented META command.
2013-02-01 update v3c and v4.1a, change value of R8 to 0R and RN1 and RN2 to 82R, unpopulate D1 on BB v3c, change value of R7 to 0R and unpopulate D1 on BB v4.1a. added final v3c and v4.1a to package folder
2013-02-11 fix ICSP 0.1 inch header pin 5 made it to a circular pad. added proto pads with 1.2mm diameter drills
2013-02-14 * Increased the offset for the ICSP holes from 2 to 4 mils.
2013-02-19 Mark pin 1 of DIP8, DIP14, DIP14W as this is automatically changed to a square pad by DRC check. Corrected SO-8's name and values labels to their proper layers
2013-02-19 Bus Blaster v4 manufacturing test package
2013-02-19 update parts list of v3c and v4.1a, copied updated parts list to /hardware folder, made manufacturing resources files for v4.1.
2013-02-28 * Renamed folder.
2013-03-07 updates on v3.8 USB connector now in micro-B All SMD LEDs are in LED603 IO shrouded header fix, notch is facing outward not much change on the USB D+ D- line just did route them to have almost the sa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
2013-03-07 revert connection of MISO, MOSI, CS and CLK like bp v3.6 MOSI-RP6 CLK-RP7 MISO-RP8 CS-RP9
2013-03-11 Added single pad with 40mil and 32 mil drill size both square and round Added SOIC 14W, 18W, 8NW, 14NW and 16NW footprints N-narrow, W-wide, NW - Narrow + Wide Added 10cm x 10cm (DP100100) in SoB
2013-03-14 Branch for testing new changes before merging them back into the main-line.
2013-03-15 added 24AA04 DIP, 25AA04, MCP3001, MCP4901, MCP9701, TC74 TO220-5 fix some text on POT symbol
2013-03-15 * Final fixes.
2013-04-03 Added: MCP4131 Digital Potentiometer Tester Probe socket QFN 12 and 16 pins 3x3cm QFN 16, 20 and 24 4x4 cm SOIC Narrow+Wide 18, 20, 24 and 28 pins
2013-04-16 Initial Folder for Test Probe Adapter
2013-04-23 added gerbmerge config creator ULP
2013-04-25 Fixed the sizing issue mentioned in http://dangerousprototypes.com/forum/viewtopic.php?f=63&t=4563&start=15#p51915
2013-05-08 moved anchor/reference point of SoB PCBs to its center
2013-06-23 * Fixed https://github.com/jawi/ols/issues/179
2013-06-25 * Improved USB command parsing.
2013-07-23 Added: MCP7940 I2C RTC with SRAM in SOIC8 and DIP8, Alternate 3 Pins Voltage Regulator to accomodate 4th pin as tab connection. Revised VREG 3 PINS now with TO-220 Horizontal footprint
2013-07-24 bus pirate: fix slashes and filename case for linux compatibility
2013-09-28 merging PyBusPirateLite branch back into mainline
2014-01-10 changed SMD SMC-A pad size from 1.60 x 1.40 to 1.40 x 1.80 changed SMD SMC-B pad size from 1.60 x 2.40 to 1.40 x 2.80 added new SMD SMC-C footprint added part MBI5026 (SOIC-24 variant) 16-Bit constan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
2014-02-03 Initial hardware files uploaded
2014-02-11 SMD Tape cutting controller intended to automatically dispense SMD parts
2014-02-11 An SMD Tape cutting controller intended to automatically dispense SMD parts
2014-02-23 SPI mode } command was giving errors, busPirateCore.c line 225 now maps to SPIstop for stopR. Should fix it. Untested.
2014-03-21 added Map of Hacker Camp Shenzen 2014 PDF
2014-03-23 changed VR1, VR2 LDO regulators to MCP1801T-3302I/OT and VR3 to MCP1801T-5002I/OT. to fix the issue on LDO output voltage oscillation due to the usage of ceramic caps on the output of each LDO. these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
2014-03-28 Parts added 74138 mux, 74244 buffer - BGA-20 7408 - DSBGA-8 CR2032 battery holder SMD part no. 1060TR SMD DIP switch 4S
2014-08-28 added bus pirate v3.8a a compact bus pirate v3.8 fitted within 5x5cm SoB board
2014-08-29 -replaced SMD version for the IO and ICSP header -fixed over hang distance of header including USB connector to 1.25mm -gerber generated
2014-09-03 board update: -changed ICSP header to 6pins, spare pin not connected -moved all LEDs a little to the right for even space
2015-10-07 Disable buffer overflow warning when in BPv4 USB mode (not debug)
2015-10-07 update gitignore
2015-11-30 Changed project url from googlecode to github
2015-12-12 QT_GUI: Fix build of QT GUI under QT5
2016-03-30 Introduce gitattributes to prevent wall of pink
2016-03-30 binIO: Fix modular code inclusion
2018-01-04 added v3.9 hardware, a SoB square bus pirate for educational purpose. Modification are: I/O pins to 10-pin JST connector and USB-min-B to USB-micro-B
2018-02-18 v5 updates
2018-02-18 Revert "v5 updates"
    This reverts commit fdefe8172c1f0e87f5b9114fcbd5650d3a1b5cb2.
2018-02-18 all versions: ASCII hybrid display mode, major/minor version variable. v5: support for new onboard pullup resistor system
2018-02-18 updated strings
2018-02-19 1. remove BUSPIRATEV1A compatibility. 2. refactor to use BP_PULLUP_OFF() everywhere on all hardware versions. 3. refactor to use BP_EXTPU_ON() everywhere in all versions where a menu is not shown
2018-02-19 renamed all BP_PULLUP(_DIR) to BP_PUVSELEXT to follow naming convention of v4 and v5 3.3volt and 5volt pullup supply select pins
2018-02-20 rework and verify v4 pullup pseudo functions
2018-02-20 reset open drain bits on mode reset
2018-02-20 remove v2.5 defines
2018-02-20 pullup resistor info for v5 hardware
2018-02-20 strings: "Power supplies" updated
2018-02-22 remove soft I2C software option. Now is compile option only.
2018-02-22 separate bus read and bus write output display format
2018-02-28 Automated build testing scripts v1
2018-03-03 updated v5 pullup source select macros. Remove mode display from I2C setup that was inconsistent with other libraries
2018-03-03 update pullup source message logic in info/status menu
2018-04-09 mplabX project for v5 CDI
2018-04-09 remove/gitignore mplabx work files
2018-04-10 git ignore make generated make files
2018-04-10 remove make files
2018-04-10 renane v3 project folder
2018-04-10 comment
2018-06-17 Support for 9-bit UART read
2019-01-01 Add mac OS BPXSVFplayer binary
